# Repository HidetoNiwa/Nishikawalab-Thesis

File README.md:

# Nishikawalab-Thesis
西川研究室における卒業論文リポジトリ
# タイトル
伸縮性導電性布を用いたフレキシブルストレッチセンサの開発と応用

―やわらかいロボットのためのやわらかいセンサの実現に向けて―
# 注意
## 画像ファイルに関して

ImageMagicでjpg,png等の画像ファイルをepsに変換する必要がある.
### 準備
1. http://www.imagemagick.org/script/index.php にてImage Magickのインストールを行う
2. コマンドプロンプトを起動し、「magick --version」と入力して、PATHが通っているか確認する
### 使用コマンド
"hoge.jpg"といった名前の画像を"hogehoge.eps"に変換したい場合、下記コマンドを画像フォルダのディレクトリで実行する。
>magick hoge.jpg eps2:hogehoge.eps

※今回はbatファイルを用意してあるのでその上にjpg等を持っていくと画像を作製してくれます。

# 構成
1. 緒言
   1. 研究背景
   2. 先行研究例
      1. フレキシブルストレッチセンサ
      2. ペダリングロボットに関して
      3. 2足歩行ロボットに関して
   3. 研究目的
   4. 論文構成
2. 実験方法
   1. 動作モデル
      1. ストレッチセンサ
      2. 静電容量計測回路
      3. 足関節ロボット
3. 解析方法
4. 結果・考察
5. 結言
6. 謝辞
7. 参考文献

# 参考文献
- MIT Soft Robotics：https://softroboticstoolkit.com/resources-for-educators/tsh-sensor

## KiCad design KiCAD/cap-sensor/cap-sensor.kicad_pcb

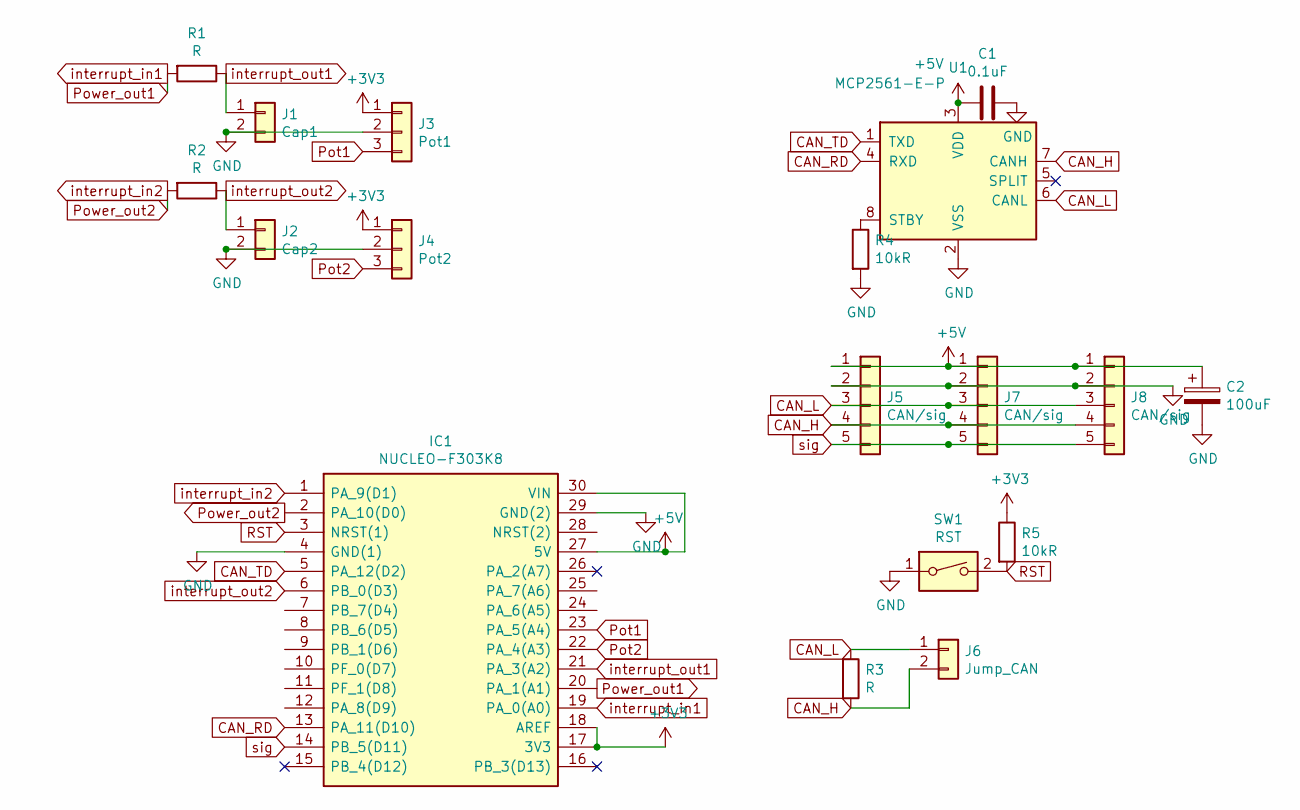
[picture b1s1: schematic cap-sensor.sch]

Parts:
C1: 0.1uF; C_0805_2012Metric_Pad1.15x1.40mm_HandSolder
C2: 100uF; CP_Radial_D5.0mm_P2.00mm
IC1: NUCLEO-F303K8; DIPS1524W66P254L5029H1500Q30N; Manufacturer_Part_Number NUCLEO-F303K8
J1: Cap1; XA_2
J2: Cap2; XA_2
J3: Pot1; XA_3
J4: Pot2; XA_3
J5, J7, J8: CAN/sig; JST_XH_B5B-XH-A_1x05_P2.50mm_Vertical
J6: Jump_CAN; PinHeader_1x02_P2.54mm_Vertical
R1, R2, R3: R; R_0805_2012Metric_Pad1.15x1.40mm_HandSolder
R4, R5: 10kR; R_0805_2012Metric_Pad1.15x1.40mm_HandSolder
SW1: RST; SW_PUSH_6mm
U1: MCP2561-E-P; DIP-8_W7.62mm

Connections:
+3V3: IC1.17 (3V3), IC1.18 (AREF), J3.1, J4.1, R5.1
+5V: C1.2, C2.1, IC1.27 (5V), IC1.30 (VIN), J5.1, J7.1, J8.1, U1.3 (VDD)
CAN_H: J5.4, J6.2, J7.4, J8.4, R3.2, U1.7 (CANH)
CAN_L: J5.3, J6.1, J7.3, J8.3, R3.1, U1.6 (CANL)
CAN_RD: IC1.13 (PA_11(D10)), U1.4 (RXD)
CAN_TD: IC1.5 (PA_12(D2)), U1.1 (TXD)
GND: C1.1, C2.2, IC1.4 (GND(1)), IC1.29 (GND(2)), J1.2, J2.2, J3.2, J4.2, J5.2, J7.2, J8.2, R4.2, SW1.1, U1.2 (VSS)
unnamed: R4.1, U1.8 (STBY)
Pot1: IC1.23 (PA_5(A4)), J3.3
Pot2: IC1.22 (PA_4(A3)), J4.3
Power_out1: IC1.19 (PA_0(A0)), IC1.20 (PA_1(A1)), R1.2
Power_out2: IC1.1 (PA_9(D1)), IC1.2 (PA_10(D0)), R2.2
RST: IC1.3 (NRST(1)), R5.2, SW1.2
interrupt_out1: IC1.21 (PA_3(A2)), J1.1, R1.1
interrupt_out2: IC1.6 (PB_0(D3)), J2.1, R2.1
sig: IC1.14 (PB_5(D11)), J5.5, J7.5, J8.5

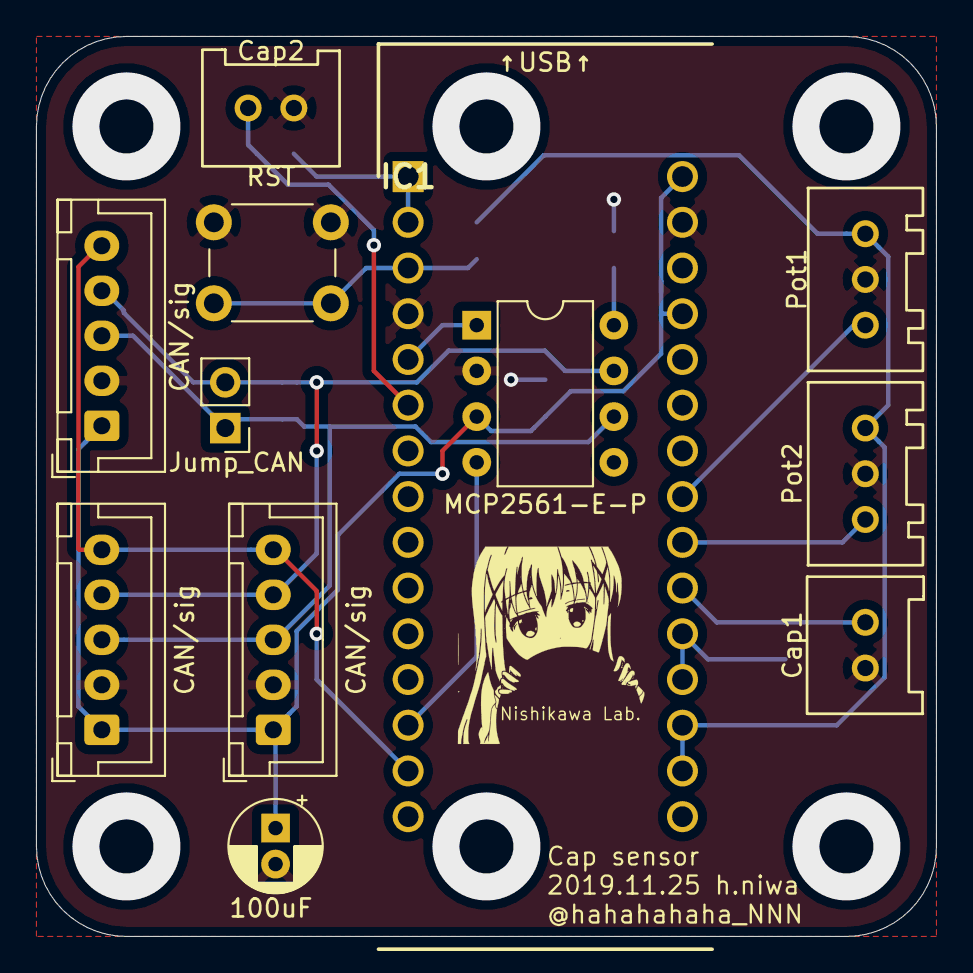
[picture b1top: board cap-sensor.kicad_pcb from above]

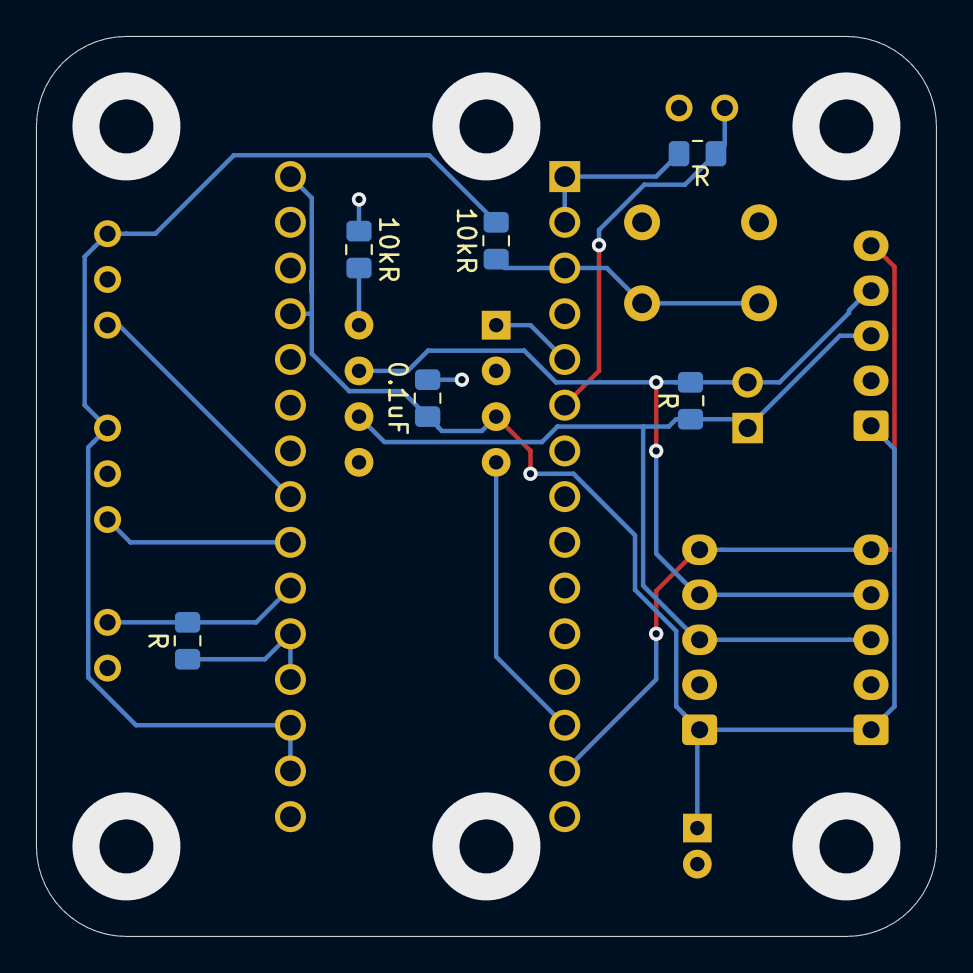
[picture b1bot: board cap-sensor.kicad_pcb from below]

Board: 2 copper layers, 50.0 x 50.0 mm, 18 parts (6 on the bottom side), 16 nets.

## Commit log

2019-12-10 add template
2019-12-10 とりあえず、表紙完成させた
2019-12-31 いらないデータを削除した（なお、うまくコンパイルができない...）
2019-12-31 研究室PCだとうまくコンパイルできる
2019-12-31 #1 下宿機でもコンパイルできるようになった、
2019-12-31 add gitignore
2019-12-31 add gitignore data
2019-12-31 gitignoreの適用
2019-12-31 余計なものを削除
2019-12-31 変更点をコミット
2019-12-31 西川研究室のPC用ブランチの作成
2019-12-31 タスクの構成を行い、Ctrl+Shift+bでコンパイル可能にした、また研究背景に関して書き進めた
2019-12-31 main.pdfを追跡しないように変更
2019-12-31 TODOを追加した
2019-12-31 写真ファイルの追加
2019-12-31 古いepsファイルを削除、画像ファイルを追加
2019-12-31 AddGitHub Actions Files
2019-12-31 最近のGitHubActionsの仕様に合わせる
2019-12-31 zemi.texをコミット
2019-12-31 Update Dockerfile
2019-12-31 platexに変更
2019-12-31 いらないソフトの除去
2019-12-31 \の追加
2019-12-31 TestAction HelloWorld
2020-01-01 回路写真追加,伸縮センサ計測回路に関して追加
2020-01-01 初号機に関して書き足した
2020-01-01 Task変更,2号機の画像位置変更
2020-01-01 KiCAD回路図追加
2020-01-01 ReadMeにレポート構成基準,余計な計測データ削除
2020-01-02 フォント埋め込みタスクを使用
2020-01-02 初号機に関して追記
2020-01-02 伸縮センサのお話を前の方にもっていき構成を少し変えた
2020-01-02 二段組を有効にした
2020-01-02 セクションごとにファイルを分割
2020-01-02 卒論用伸縮センサ図解CADを追加
2020-01-02 TeXファイルをセクションごとに分割
2020-01-02 余計なファイルを削除
2020-01-02 図面式の説明画像を生成した
2020-01-02 CADレンダリング式画像追加
2020-01-03 伸縮センサ説明図追加
2020-01-28 先輩からのTeX資料をコミット、自分が作成中のものとマージを行う予定
2020-01-28 Edit Read.MD png画像等の貼り付けにも対応した
2020-01-28 一部、espファイルの削除
2020-01-28 仮タイトル制定、自分の文章移植
2020-01-28 余計な資料削除、博論追加
2020-01-28 先行研究例（ペダリングロボット）までは記述完了、2号機に関する記述を行う必要があり
2020-01-29 #13 空気圧人工筋に関する筋肉の記述を行った 筋肉の数、研究論文、要確認
2020-01-29 #11 タイトル決定
    これで教務に提出する
2020-01-29 Figure Dir変更
2020-01-29 ebbを用いる方式からepsを用いる方法に変更
2020-01-29 改ページ挿入
2020-01-29 オシロスコープ画像の追加を行った、RC回路の説明を数式を含めて行った
2020-01-30 二足歩行ロボットに関する記述増加
    横向き画像を増加させる必要あり
2020-01-30 画像資料、論文追加、伸縮センサ理論追加
2020-01-30 Update tex.yml
    TeXコンパイラインストールコマンド入れた
2020-01-31 edit githubActions（byQiita）
2020-01-31 pathの変更
2020-01-31 以前のymlに修正
2020-01-31 verの変更
2020-01-31 Rename DockerFile to Dockerfile
2020-01-31 renamePath
2020-01-31 画像ディレクトリ変更（緒言のみ）
2020-01-31 {の個数変更
2020-01-31 インストールするものを増加
2020-01-31 ローカルでの動作確認済み
2020-01-31 画像ディレクトリ変更
2020-01-31 Dir表記変更
2020-01-31 JP名をEN名に
2020-01-31 shell Edit
2020-01-31 画像ソフトインストール
2020-01-31 releaseでコンパイルを行うよう設定
2020-01-31 releaseブランチのみに限定
2020-01-31 タグを日時に変更
2020-01-31 ないコマンド削除
2020-01-31 日時でタグ付くように修正
2020-01-31 どうさするものに最終修正
2020-01-31 URL指定にミスがあったので修正
2020-01-31 伸縮センサの紹介記載
2020-02-01 論文構成の修正、研究目的の追記
2020-02-02 足関節における筋肉の話を記述（付着位置とかはまた記述した方がいいかも）
2020-02-02 #31 記述位置すべて変更
2020-02-02 足関節ロボット製作方法の記述、画像の挿入
2020-02-03 Update analysis.tex
    mbedに関して少し記述
2020-02-04 ストレッチセンサ計測アルゴリズム記述
2020-02-04 #34 伸縮センサをストレッチセンサに変更
2020-02-05 画像追加、KiCADデータ追加
2020-02-05 結果を一部記入
2020-02-05 ストレッチセンサ製作過程を記述
2020-02-05 実験結果を記入
2020-02-06 空気圧人工筋システムに関して記述
2020-02-06 最新の結果を記述
2020-02-06 センサ精度評価に関して記述
2020-02-07 残り、結果/考察/結言で完成
2020-02-08 参考文献追加、緒言記述変更
2020-02-08 とりあえず、残り結言だけ記述すれば完成
    動的解析のデータも入れられたら入れる。
2020-02-09 とりあえずの最終版
    結言記入、句読点の修正完了
2020-02-09 精度評価用の図追加
2020-02-09 リファレンス追加
2020-02-14 動的試験のグラフ作成、グラフ挿入済み
2020-02-16 結果、一部追記
2020-02-16 考察用画像作成
2020-02-16 動的計測の考察記述途中
2020-02-17 最終版完成
2020-11-19 edit Docker file
